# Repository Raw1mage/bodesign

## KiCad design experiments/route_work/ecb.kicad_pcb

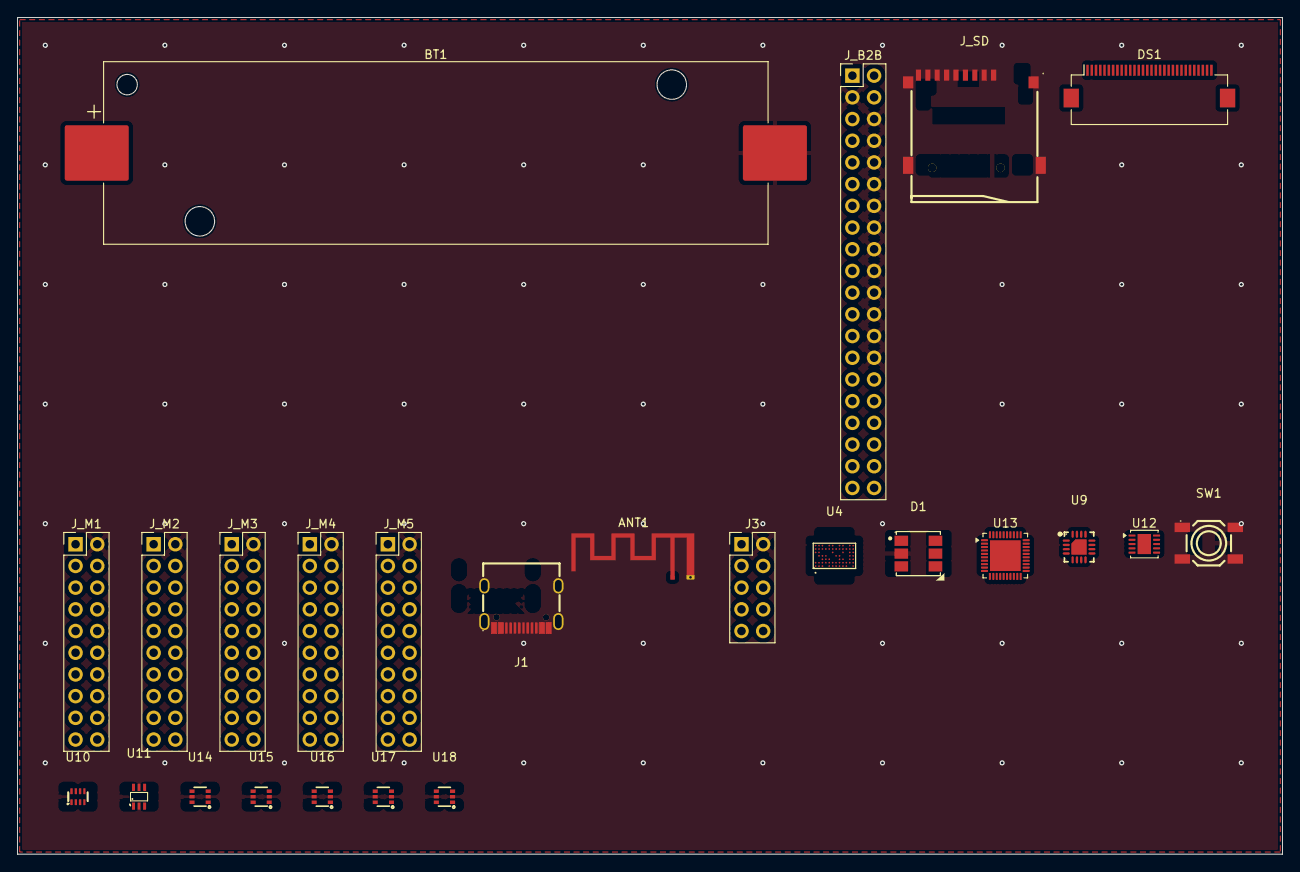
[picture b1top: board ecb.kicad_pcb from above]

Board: 4 copper layers, 148.1 x 97.9 mm, 25 parts (0 on the bottom side), 21 nets, no tracks yet.

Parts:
ANT1: 2.4GHz antenna; Texas_SWRA117D_2.4GHz_Left
BT1: 18650 holder; BatteryHolder_Keystone_1042_1x18650
D1: RGB LED; LED-SMD_6P-L5.0-W5.0-FD
DS1: touch OLED FPC; Hirose_FH12-30S-0.5SH_1x30-1MP_P0.50mm_Horizontal
J1: USB-C; USB-C_SMD-TYPE-C-31-M-12_1
J3: SWD; PinHeader_2x05_P2.54mm_Vertical
J_B2B: CCM-ECB B2B (visual stand-in, MPN open); PinHeader_2x20_P2.54mm_Vertical
J_M1: module port 1; PinHeader_2x10_P2.54mm_Vertical
J_M2: module port 2; PinHeader_2x10_P2.54mm_Vertical
J_M3: module port 3; PinHeader_2x10_P2.54mm_Vertical
J_M4: module port 4; PinHeader_2x10_P2.54mm_Vertical
J_M5: module port 5; PinHeader_2x10_P2.54mm_Vertical
J_SD: microSD; TF-SMD_TF-01A
SW1: button; SW-SMD_4P-L5.2-W5.2-P3.70-LS6.4-TS-076S-030180-P
U4: WiFi/BLE module placeholder; WLBGA-63_L4.8-W2.8-P0.40-BL_CYW43438KUBGT
U9: BQ24075 charger; QFN-16_L3.0-W3.0-P0.50-TL-EP1.7
U10: LM66200 OR-ing; SOT-583-8_L2.1-W1.2-P0.50-LS1.6-BL
U11: LM66100 power-path; SC-70-6_L2.0-W1.3-P0.65-LS2.1-BL
U12: USB ESD; DFN-10-1EP_3x3mm_P0.5mm_EP1.58x2.35mm
U13: MIPI mux block; QFN-40-1EP_5x5mm_P0.4mm_EP3.6x3.6mm
U14: load switch P1; SC-70-6_L2.2-W1.3-P0.65-LS2.1-BR
U15: load switch P2; SC-70-6_L2.2-W1.3-P0.65-LS2.1-BR
U16: load switch P3; SC-70-6_L2.2-W1.3-P0.65-LS2.1-BR
U17: load switch P4; SC-70-6_L2.2-W1.3-P0.65-LS2.1-BR
U18: load switch P5; SC-70-6_L2.2-W1.3-P0.65-LS2.1-BR

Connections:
+3V3: DS1.1, J3.1, J_B2B.4, J_B2B.5, U13.1
BOOT0: J3.8, J_B2B.15
GND: ANT1.2, BT1.2, D1.2, DS1.2, J3.2, J_B2B.3, J_B2B.6, J_B2B.8, J_B2B.10, J_B2B.12, J_B2B.14, J_B2B.16, J_B2B.18, J_B2B.20, J_B2B.22, J_B2B.24, J_B2B.26, J_B2B.28, J_M1.2, J_M2.2, J_M3.2, J_M4.2, J_M5.2, J_SD.2, SW1.2, U9.2, U10.2, U11.2, U14.2, U15.2, U16.2, U17.2, U18.2
MIPI_PLACEHOLDER_1: J_B2B.17, U13.2
MIPI_PLACEHOLDER_2: J_B2B.19, U13.3
MIPI_PLACEHOLDER_3: J_B2B.21, U13.4
MIPI_PLACEHOLDER_4: J_B2B.23, U13.5
MIPI_PLACEHOLDER_5: J_B2B.25, U13.6
MIPI_PLACEHOLDER_6: J_B2B.27, U13.7
NRST: J3.10, J_B2B.13
SYS: J_B2B.1, J_B2B.2, U9.8, U10.3, U11.3
USB_CC1: J1.A7, J_B2B.11
USB_DM: J_B2B.9, U12.3
USB_DP: J1.A8, J_B2B.7, U12.2
VBAT_CELL: BT1.1, U9.5, U10.1
VBUS_5V: J1.A6, U9.1, U12.1
VMOD1: J_M1.1, U14.5
VMOD2: J_M2.1, U15.5
VMOD3: J_M3.1, U16.5
VMOD4: J_M4.1, U17.5
VMOD5: J_M5.1, U18.5

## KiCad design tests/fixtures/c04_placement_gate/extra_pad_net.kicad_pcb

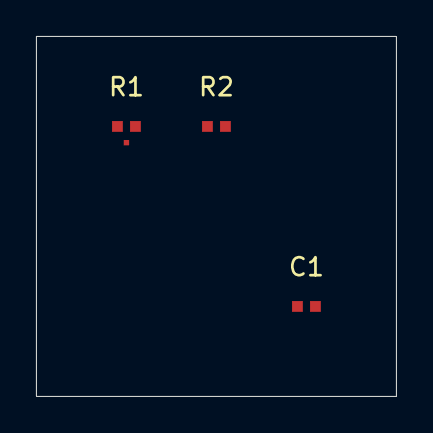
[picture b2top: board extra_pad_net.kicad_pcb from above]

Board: 2 copper layers, 20.0 x 20.0 mm, 3 parts (0 on the bottom side), 3 nets, no tracks yet.

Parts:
C1: C_0402_1005Metric
R1, R2: R_0402_1005Metric

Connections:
GND: C1.2, R2.2
N1: C1.1, R1.1, R1.3
N2: R1.2, R2.1
